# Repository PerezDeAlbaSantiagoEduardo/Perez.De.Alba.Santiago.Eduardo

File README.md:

# Perez.De.Alba.Santiago.Eduardo

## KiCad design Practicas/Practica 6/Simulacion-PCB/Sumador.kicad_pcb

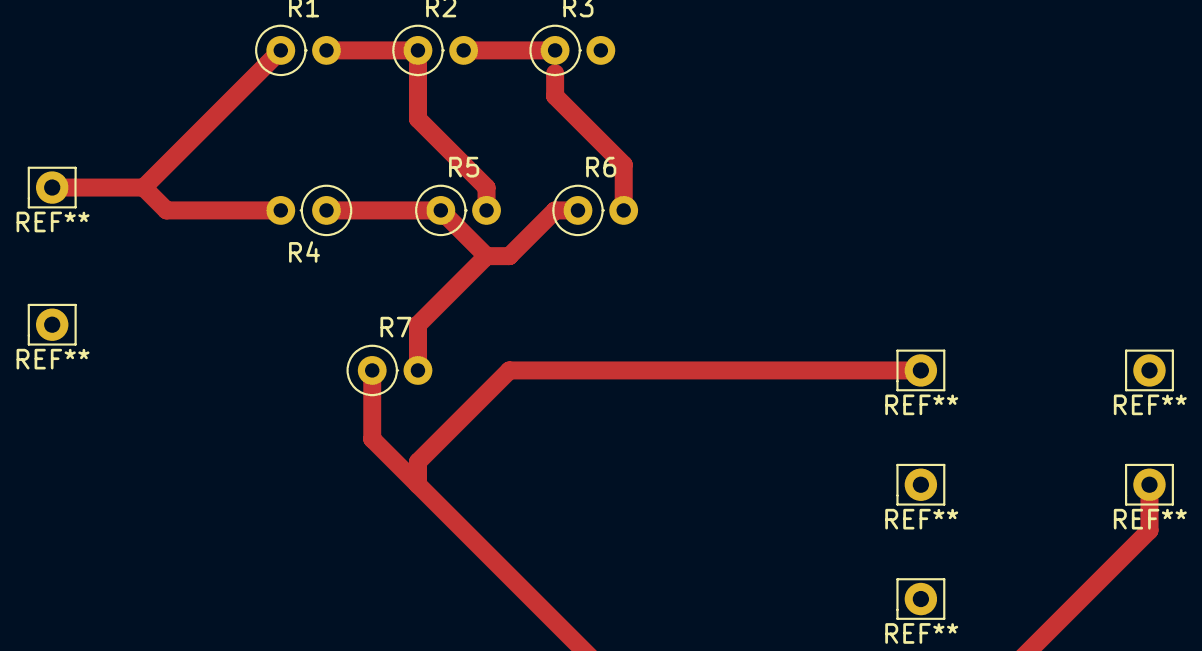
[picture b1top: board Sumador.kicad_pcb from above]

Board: 2 copper layers, 7 parts (0 on the bottom side), 4 nets.

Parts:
R1, R2, R3, R4, R5, R6, R7: R; R_Axial_DIN0207_L6.3mm_D2.5mm_P2.54mm_Vertical

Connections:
unnamed: R1.1, R4.2
unnamed: R1.2, R2.1, R5.2
unnamed: R2.2, R3.1, R6.2
unnamed: R4.1, R5.1, R6.1, R7.2

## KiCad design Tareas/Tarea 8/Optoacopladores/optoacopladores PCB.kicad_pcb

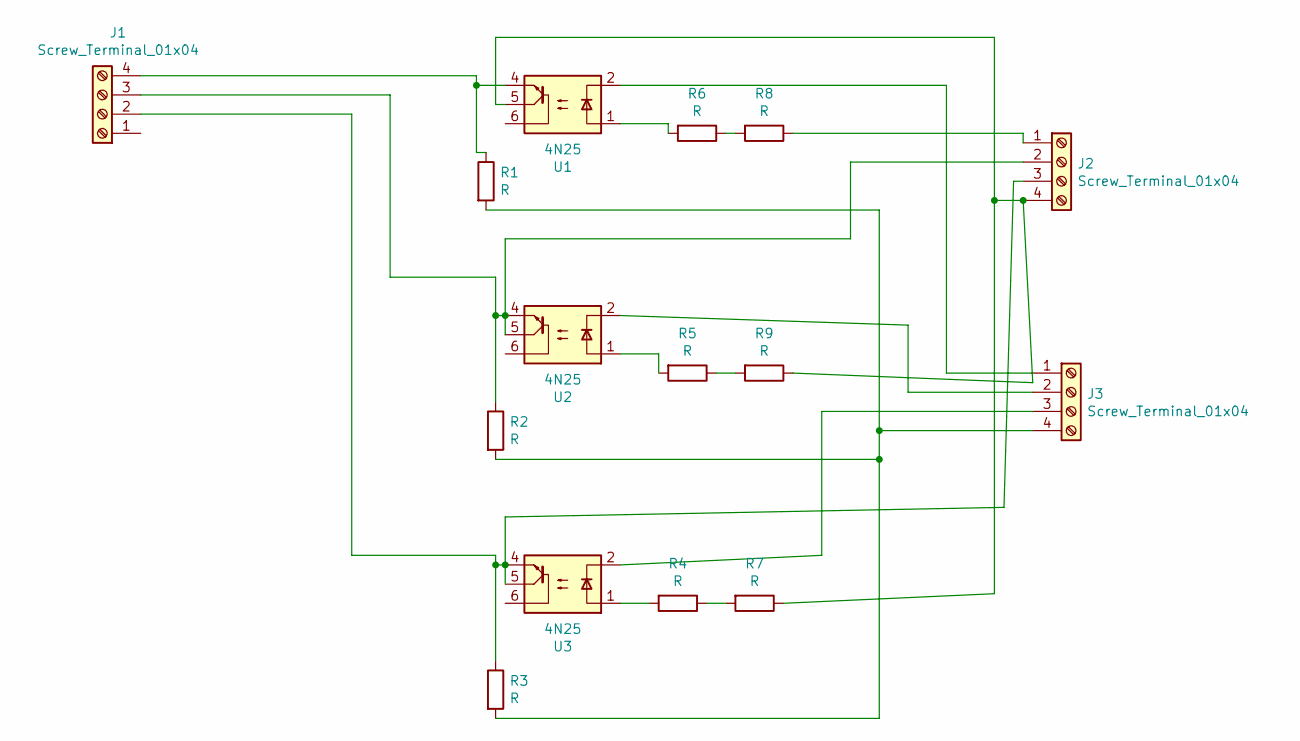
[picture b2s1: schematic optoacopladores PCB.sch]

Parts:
J1, J2, J3: Screw_Terminal_01x04; TerminalBlock_Wuerth_691311400102_P7.62mm
R1: R; R_Axial_DIN0207_L6.3mm_D2.5mm_P10.16mm_Horizontal
R2, R3, R4, R5, R6, R7, R8, R9: R; R_Axial_DIN0204_L3.6mm_D1.6mm_P5.08mm_Vertical
U1, U2, U3: 4N25; DIP-6_W7.62mm

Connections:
unnamed: J1.2, J2.3, R3.1, U3.4, U3.5
unnamed: J1.3, J2.2, R2.1, U2.4, U2.5
unnamed: J1.4, R1.1, U1.4
unnamed: J2.1, R8.1
unnamed: J2.4, R7.1, R9.1, U1.5
unnamed: J3.1, U1.2
unnamed: J3.2, U2.2
unnamed: J3.3, U3.2
unnamed: J3.4, R1.2, R2.2, R3.2
unnamed: R4.1, R7.2
unnamed: R4.2, U3.1
unnamed: R5.1, R9.2
unnamed: R5.2, U2.1
unnamed: R6.1, R8.2
unnamed: R6.2, U1.1

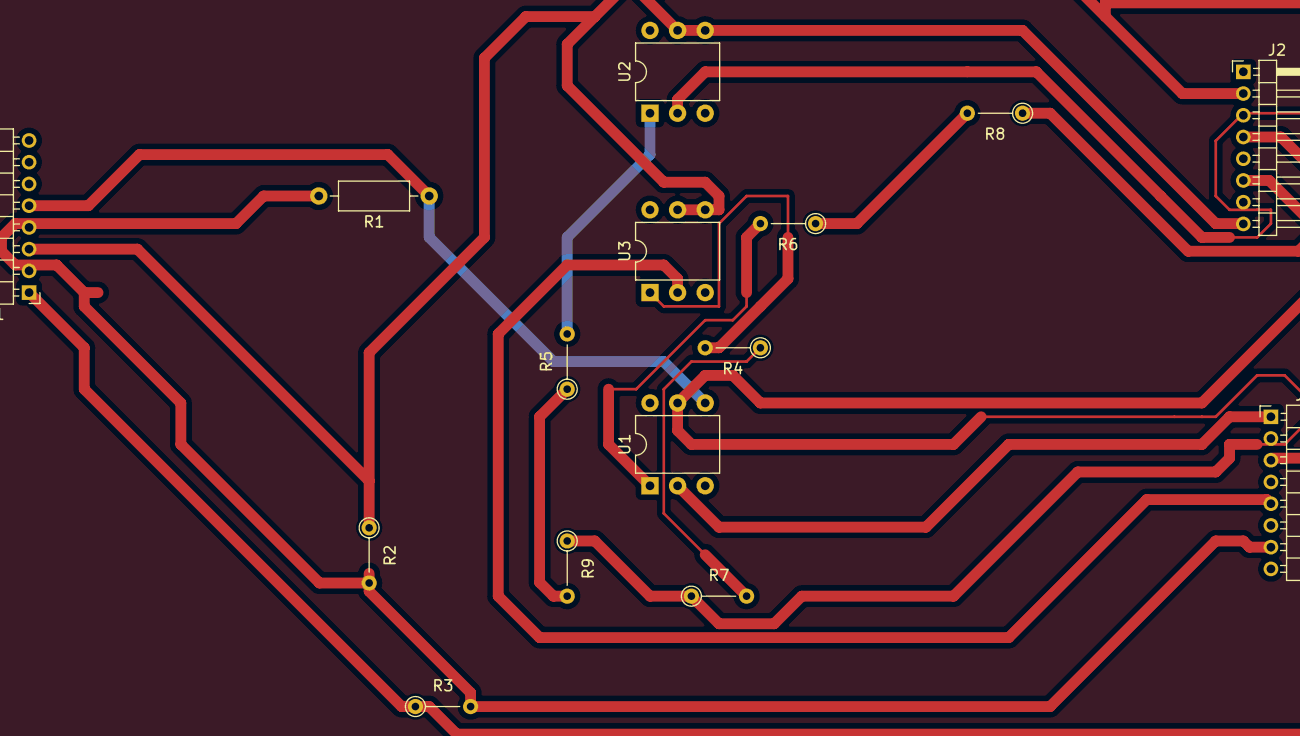
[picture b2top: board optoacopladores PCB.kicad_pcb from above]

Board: 2 copper layers, 15 parts (0 on the bottom side), 15 nets.

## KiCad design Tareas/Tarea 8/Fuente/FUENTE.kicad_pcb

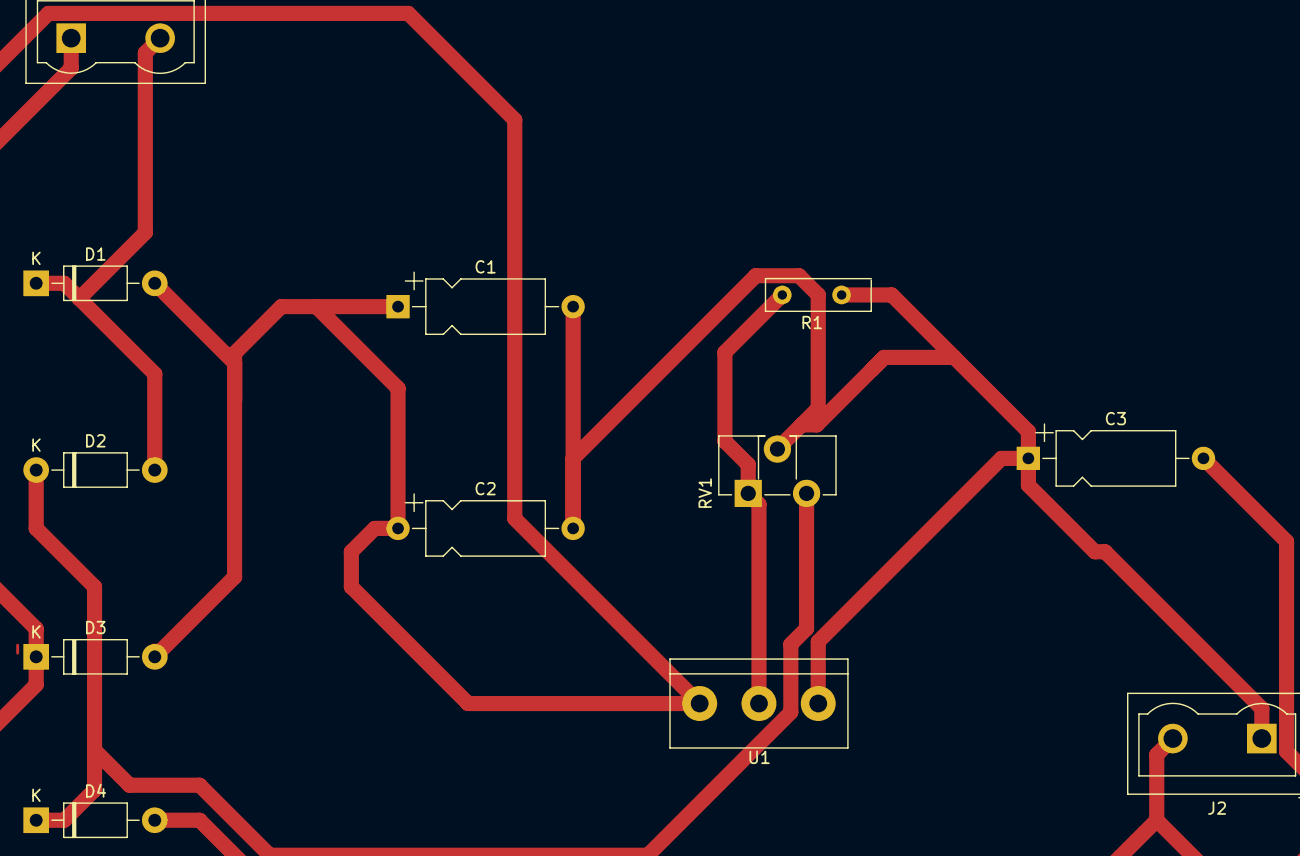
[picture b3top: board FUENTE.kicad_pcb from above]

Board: 2 copper layers, 12 parts (0 on the bottom side), 5 nets.

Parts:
C1: 2200uF; CP_Axial_L10.0mm_D4.5mm_P15.00mm_Horizontal
C2: 0.1uF; CP_Axial_L10.0mm_D4.5mm_P15.00mm_Horizontal
C3: 270uF; CP_Axial_L10.0mm_D4.5mm_P15.00mm_Horizontal
D1, D2, D3, D4: 1N4007; D_DO-41_SOD81_P10.16mm_Horizontal
J1, J2: Screw_Terminal_01x02; TerminalBlock_Wuerth_691311400102_P7.62mm
R1: 10K; R_Array_SIP4
RV1: 5K; Potentiometer_ACP_CA9-H3,8_Horizontal
U1: LM317_TO3; TerminalBlock_bornier-3_P5.08mm

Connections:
unnamed: R1.4, RV1.1, U1.2
unnamed: C1.2, C2.2, C3.1, J2.1, R1.2, RV1.2, U1.1
unnamed: D1.1, D2.2, D3.1, D4.2, J1.1, J1.2
unnamed: C1.1, C2.1, C3.2, D1.2, D3.2, J2.2, U1.3
unnamed: D2.1, D4.1, RV1.3

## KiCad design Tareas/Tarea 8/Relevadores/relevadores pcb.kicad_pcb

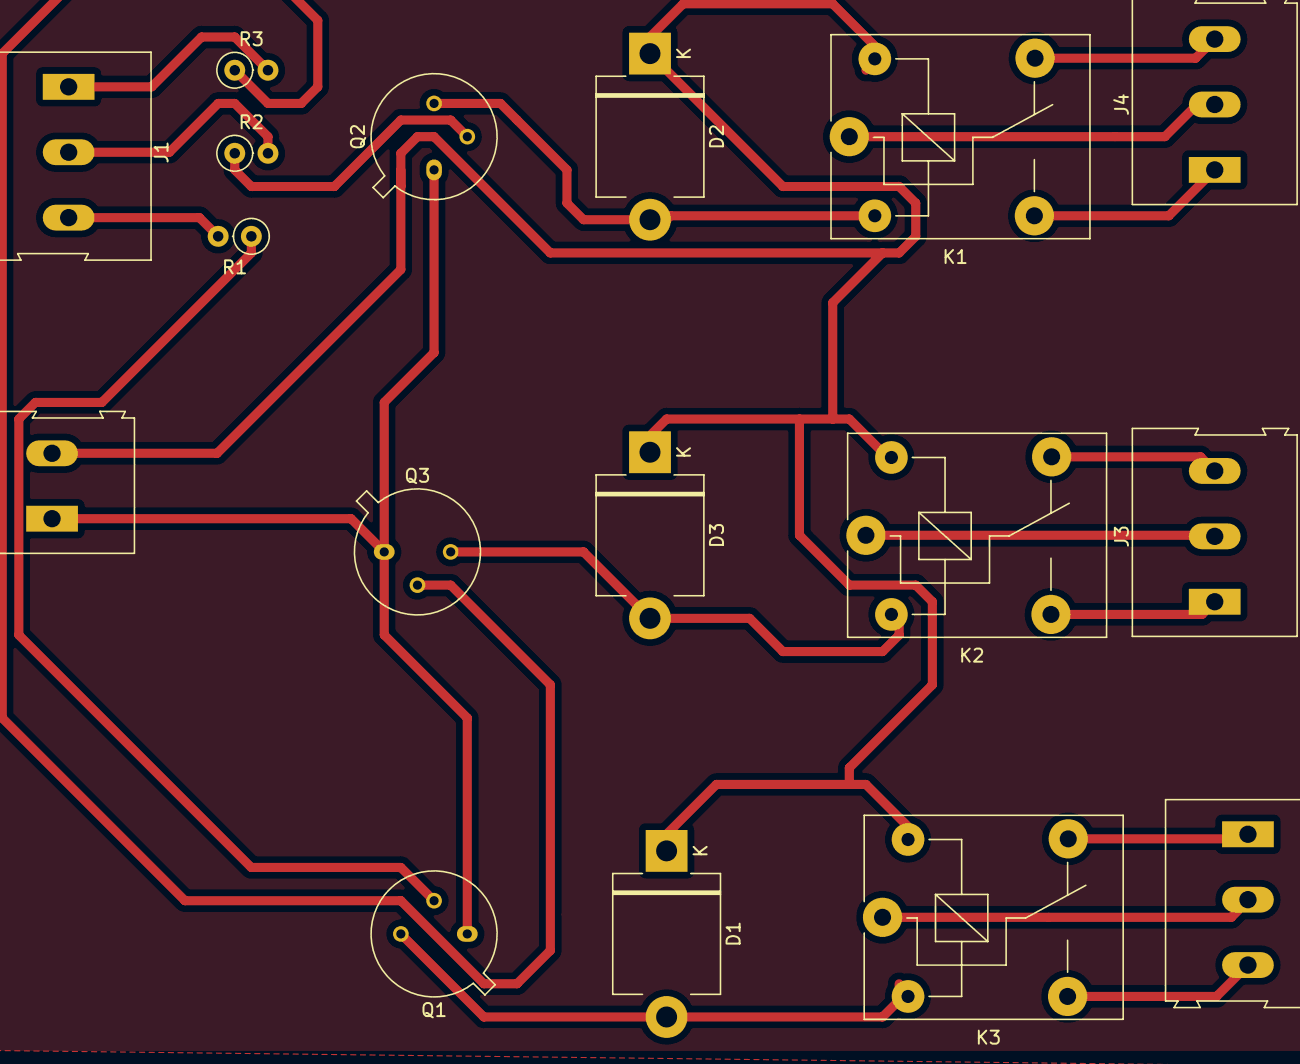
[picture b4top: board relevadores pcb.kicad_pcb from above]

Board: 2 copper layers, 17 parts (0 on the bottom side), 14 nets.

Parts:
D1, D2, D3: D; D_5KPW_P12.70mm_Horizontal
J1, J3, J4, J5: Screw_Terminal_01x03; TerminalBlock_Altech_AK300-3_P5.00mm
J2: Screw_Terminal_01x02; TerminalBlock_Altech_AK300-2_P5.00mm
K1, K2, K3: HF3-03; Relay_SPDT_SANYOU_SRD_Series_Form_C
Q1, Q2, Q3: 2N2219; TO-39-3
R1, R2, R3: R; R_Axial_DIN0207_L6.3mm_D2.5mm_P2.54mm_Vertical

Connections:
unnamed: D1.1, D2.1, D3.1, J2.2, K1.1, K2.1, K3.1
unnamed: D1.2, Q1.3
unnamed: D2.2, Q2.3
unnamed: D3.2, Q3.3
unnamed: J1.1, R3.2
unnamed: J1.2, R2.2
unnamed: J1.3, R1.2
unnamed: J2.1, Q1.1, Q2.1, Q3.1
unnamed: J3.3, K2.2, K2.5
unnamed: J4.3, K1.2, K1.5
unnamed: J5.3, K3.2, K3.5
unnamed: Q1.2, R1.1
unnamed: Q2.2, R2.1
unnamed: Q3.2, R3.1

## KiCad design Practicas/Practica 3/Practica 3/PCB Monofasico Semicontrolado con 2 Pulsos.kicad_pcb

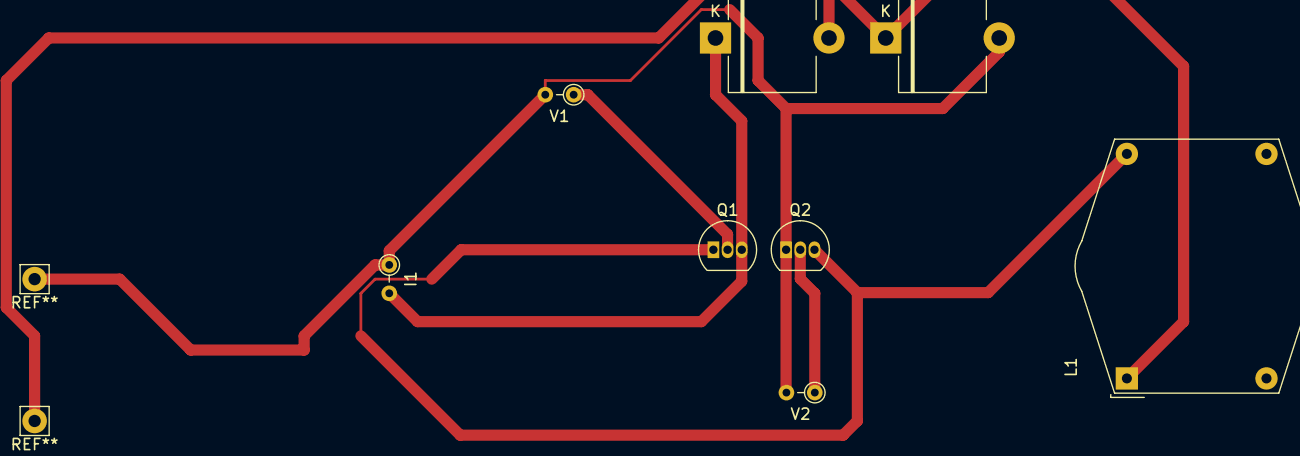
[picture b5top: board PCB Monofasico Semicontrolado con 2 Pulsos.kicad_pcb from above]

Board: 2 copper layers, 8 parts (0 on the bottom side), 6 nets.

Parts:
D1, D2: D; D_5KP_P10.16mm_Horizontal
I1: ISOURCE; R_Axial_DIN0204_L3.6mm_D1.6mm_P2.54mm_Vertical
L1: L; Choke_Schaffner_RN114-04-22.5x21.5mm
Q1, Q2: BT169B; TO-92_Inline
V1, V2: VPULSE; R_Axial_DIN0204_L3.6mm_D1.6mm_P2.54mm_Vertical

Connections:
Earth: D2.2, I1.1, Q2.1, V1.2, V2.2
unnamed: D1.1, I1.2, Q1.3
unnamed: L1.2, Q1.1, Q2.3
unnamed: Q1.2, V1.1
unnamed: Q2.2, V2.1
VAC: D1.2, D2.1, L1.1

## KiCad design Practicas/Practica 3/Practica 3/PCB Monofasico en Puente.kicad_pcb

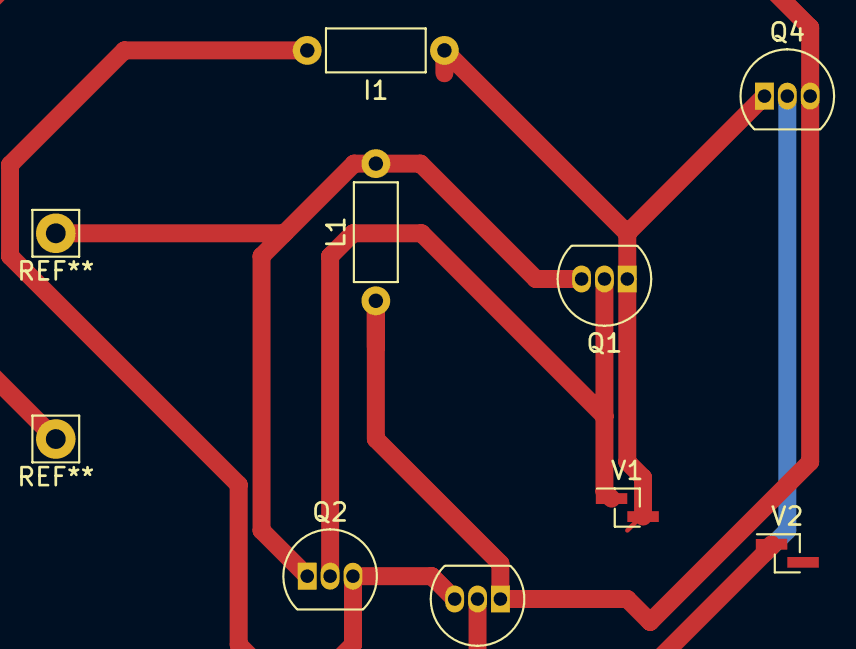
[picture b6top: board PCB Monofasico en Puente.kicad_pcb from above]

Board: 2 copper layers, 8 parts (0 on the bottom side), 6 nets.

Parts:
I1: ISOURCE; L_Axial_L5.3mm_D2.2mm_P7.62mm_Horizontal_Vishay_IM-1
L1: L; L_Axial_L5.3mm_D2.2mm_P7.62mm_Horizontal_Vishay_IM-1
Q1, Q2, Q3, Q4: BT169B; TO-92_Inline
V1, V2: VPULSE; PinHeader_1x02_P1.00mm_Vertical_SMD_Pin1Left

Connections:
Earth: I1.1, Q1.1, Q4.1, V1.2, V2.2
unnamed: I1.2, Q2.3, Q3.3
unnamed: L1.2, Q1.3, Q2.1
unnamed: Q1.2, Q2.2, V1.1
unnamed: Q3.2, Q4.2, V2.1
VAC: L1.1, Q3.1, Q4.3

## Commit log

2019-09-13 Carpeta para reportes
2019-09-17 EV_ 1_ 5_ características de los convertidores de potencia CA-CD, CD-CA, CA-CA y CD-CD
    Primer Tarea
2019-09-20 EV_1_2_OptoAcopladores_y_Relevadores
2019-09-20 EV_1_1_Circuitos_de_rectificación_no_controlados
2019-09-21 Avance 1
2019-09-25 EV_1_6_Explicar_la_operación_de_los_circuitos_de_activación_con_tiristores_en_convertidores_CA-CD_y_CA-CA.
2019-10-02 EV_2_2_Explicar_los_arreglos_y_parámetros_de_los_Amplificadores_Clase_A
2019-10-04 Ev_ 1_ 2_Optoacopladores_y_ Relevadores
2019-10-08 EV_2_3_Explicar_los_arreglos_y_parámetros_de_los_Amplificadores_Clase_B
2019-10-10 Primer Avance
2019-10-15 EV_2_4_giro_de_un_motor_de_corriente_directa.
2019-10-19 Segundo Avance
2019-10-23 EV_2_7_Diseño de un Modulación de ancho de pulso (PWM)
2019-10-26 EV_1_3_circuitos_de_control_de_voltaje_y_corriente_con_tiristores.
2019-10-27 EV_2_1_Diseño_del_puente_H
2019-10-30 EV_2_8 Calcular los parametros de circuitos de activacion de transistores de potencia
2019-11-06 Ev_3_4_Diseño_y_fabricacion_de_3_Pcb_con_optoacopladores_transistores_relevadores_como_sistema_de_interfaz_y_probarla_en_la_practica_10
2019-11-08 2_5_arreglos_de_amplificadores_de_potencia
2019-11-08 2_6_Construir_un_amplificación_con_conexión_Darlington
2019-11-09 Reporte Final
2019-11-11 Practica 8
2019-11-11 Ev_3_1_Diagrama_electrico_de_la_interfaz_de_potencia
